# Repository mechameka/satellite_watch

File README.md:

# satellite_watch
ESP32-S3 based smartwatch with swappable, modular faceplate

Phase 1: Create prototype large-format board for diagnosing
Phase 2: Create compact mainboard
Phase 3: Create intial faceplate designs of LED, IPS, and blank protoboard/headers

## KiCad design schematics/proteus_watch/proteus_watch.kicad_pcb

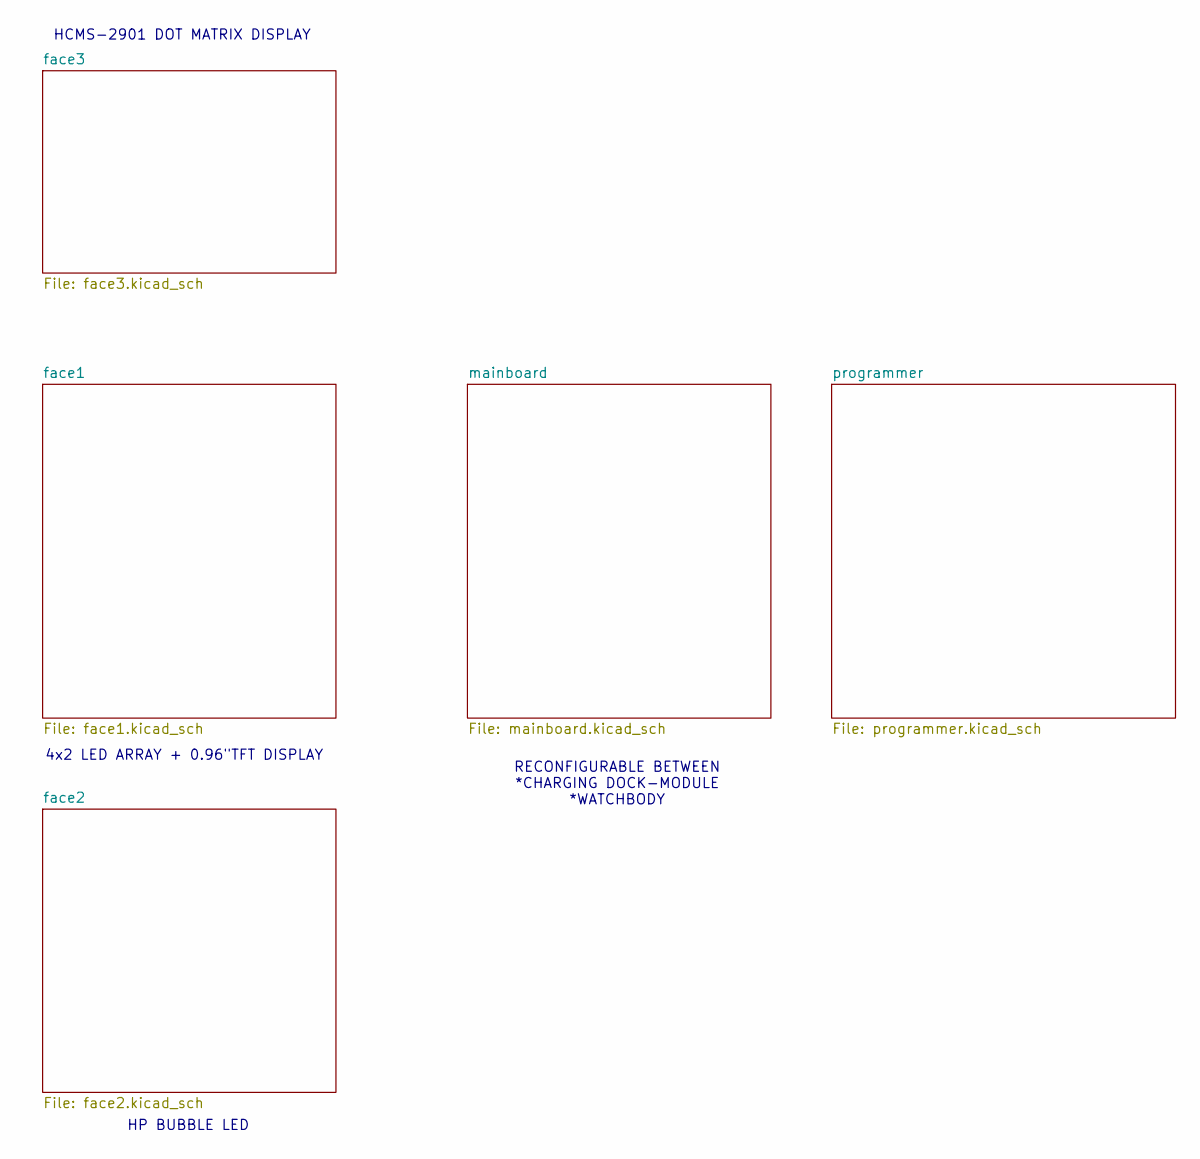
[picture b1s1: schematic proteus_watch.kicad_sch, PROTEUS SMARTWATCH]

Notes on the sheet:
RECONFIGURABLE BETWEEN *CHARGING DOCK-MODULE *WATCHBODY
4x2 LED ARRAY + 0.96"TFT DISPLAY
HCMS-2901 DOT MATRIX DISPLAY
HP BUBBLE LED

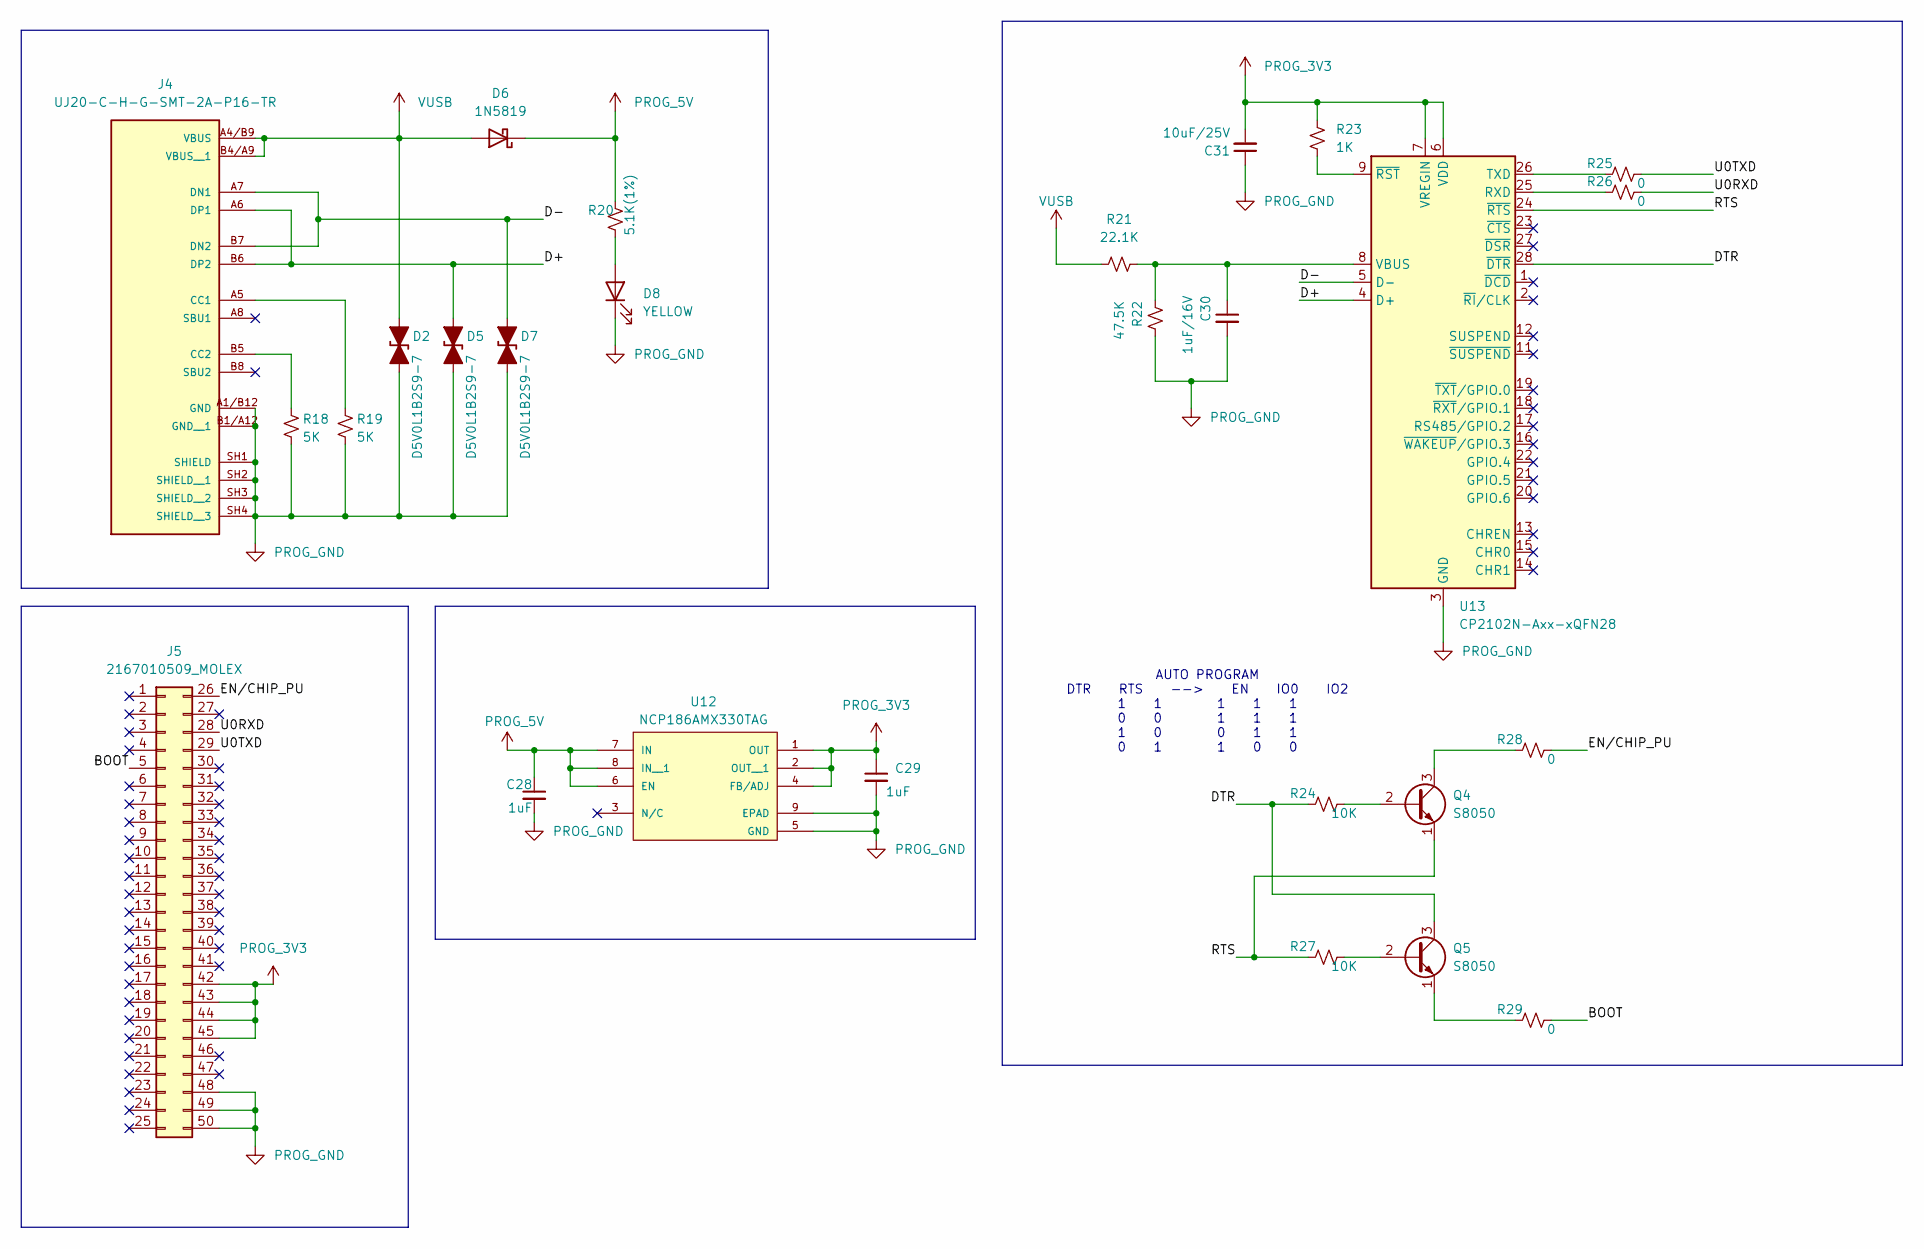
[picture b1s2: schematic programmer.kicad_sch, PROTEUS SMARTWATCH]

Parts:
C28, C29: 1uF; C_0402_1005Metric_Pad0.74x0.62mm_HandSolder
C30: 1uF/16V; C_0402_1005Metric_Pad0.74x0.62mm_HandSolder
C31: 10uF/25V; C_0402_1005Metric_Pad0.74x0.62mm_HandSolder
D2, D5, D7: D5V0L1B2S9-7; D_SOD-923
D6: 1N5819; D_SOD-123
D8: YELLOW; LED_0402_1005Metric_Pad0.77x0.64mm_HandSolder
J4: UJ20-C-H-G-SMT-2A-P16-TR; SAMESKY_UJ20-C-H-G-SMT-2A-P16-TR_1; PARTREV 1.0
J5: 2167010509_MOLEX; CON_2167010509_MOL
Q4, Q5: S8050; SOT-23
R18, R19: 5K; R_0402_1005Metric_Pad0.72x0.64mm_HandSolder
R20: 5.1K(1%); R_0402_1005Metric_Pad0.72x0.64mm_HandSolder
R21: 22.1K; R_0402_1005Metric_Pad0.72x0.64mm_HandSolder
R22: 47.5K; R_0402_1005Metric_Pad0.72x0.64mm_HandSolder
R23: 1K; R_0402_1005Metric_Pad0.72x0.64mm_HandSolder
R24, R27: 10K; R_0402_1005Metric_Pad0.72x0.64mm_HandSolder
R25, R26, R28, R29: 0; R_0402_1005Metric_Pad0.72x0.64mm_HandSolder
U12: NCP186AMX330TAG; PSON40P160X120X45-9N; PARTREV Rev.5
U13: CP2102N-Axx-xQFN28; QFN-28-1EP_5x5mm_P0.5mm_EP3.25x3.25mm_ThermalVias

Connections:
/programmer/BOOT: J5.5, R29.1
/programmer/D+: D5.1 (A1), J4.A6 (DP1), J4.B6 (DP2), U13.4 (D+)
/programmer/D-: D7.1 (A1), J4.A7 (DN1), J4.B7 (DN2), U13.5 (D-)
/programmer/DTR: Q5.3 (C), R24.2, U13.28 (~DTR)
/programmer/EN/CHIP_PU: J5.26, R28.1
/programmer/RTS: Q4.1 (E), R27.2, U13.24 (~RTS)
/programmer/U0RXD: J5.28, R26.1
/programmer/U0TXD: J5.29, R25.1
unnamed: D8.2 (A), R20.1
unnamed: J4.A5 (CC1), R19.1
unnamed: J4.B5 (CC2), R18.1
unnamed: Q4.2 (B), R24.1
unnamed: Q4.3 (C), R28.2
unnamed: Q5.2 (B), R27.1
unnamed: Q5.1 (E), R29.2
unnamed: R26.2, U13.25 (RXD)
unnamed: R25.2, U13.26 (TXD)
unnamed: C30.1, R21.2, R22.1, U13.8 (VBUS)
unnamed: R23.1, U13.9 (~RST)
PROG_3V3: C29.1, C31.2, J5.42, J5.43, J5.44, J5.45, R23.2, U12.1 (OUT), U12.2 (OUT__1), U12.4 (FB/ADJ), U13.6 (VDD), U13.7 (VREGIN)
PROG_5V: C28.1, D6.1 (K), R20.2, U12.6 (EN), U12.7 (IN), U12.8 (IN__1)
PROG_GND: C28.2, C29.2, C30.2, C31.1, D2.2 (A2), D5.2 (A2), D7.2 (A2), D8.1 (K), J4.A1/B12 (GND), J4.B1/A12 (GND__1), J4.SH1 (SHIELD), J4.SH2 (SHIELD__1), J4.SH3 (SHIELD__2), J4.SH4 (SHIELD__3), J5.48, J5.49, J5.50, R18.2, R19.2, R22.2, U12.5 (GND), U12.9 (EPAD), U13.3 (GND), U13.29 (GND)
VUSB: D2.1 (A1), D6.2 (A), J4.A4/B9 (VBUS), J4.B4/A9 (VBUS__1), R21.1

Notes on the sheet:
AUTO PROGRAM DTR RTS --> EN IO0 IO2 1 1 1 1 1 0 0 1 1 1 1 0 0 1 1 0 1 1 0 0

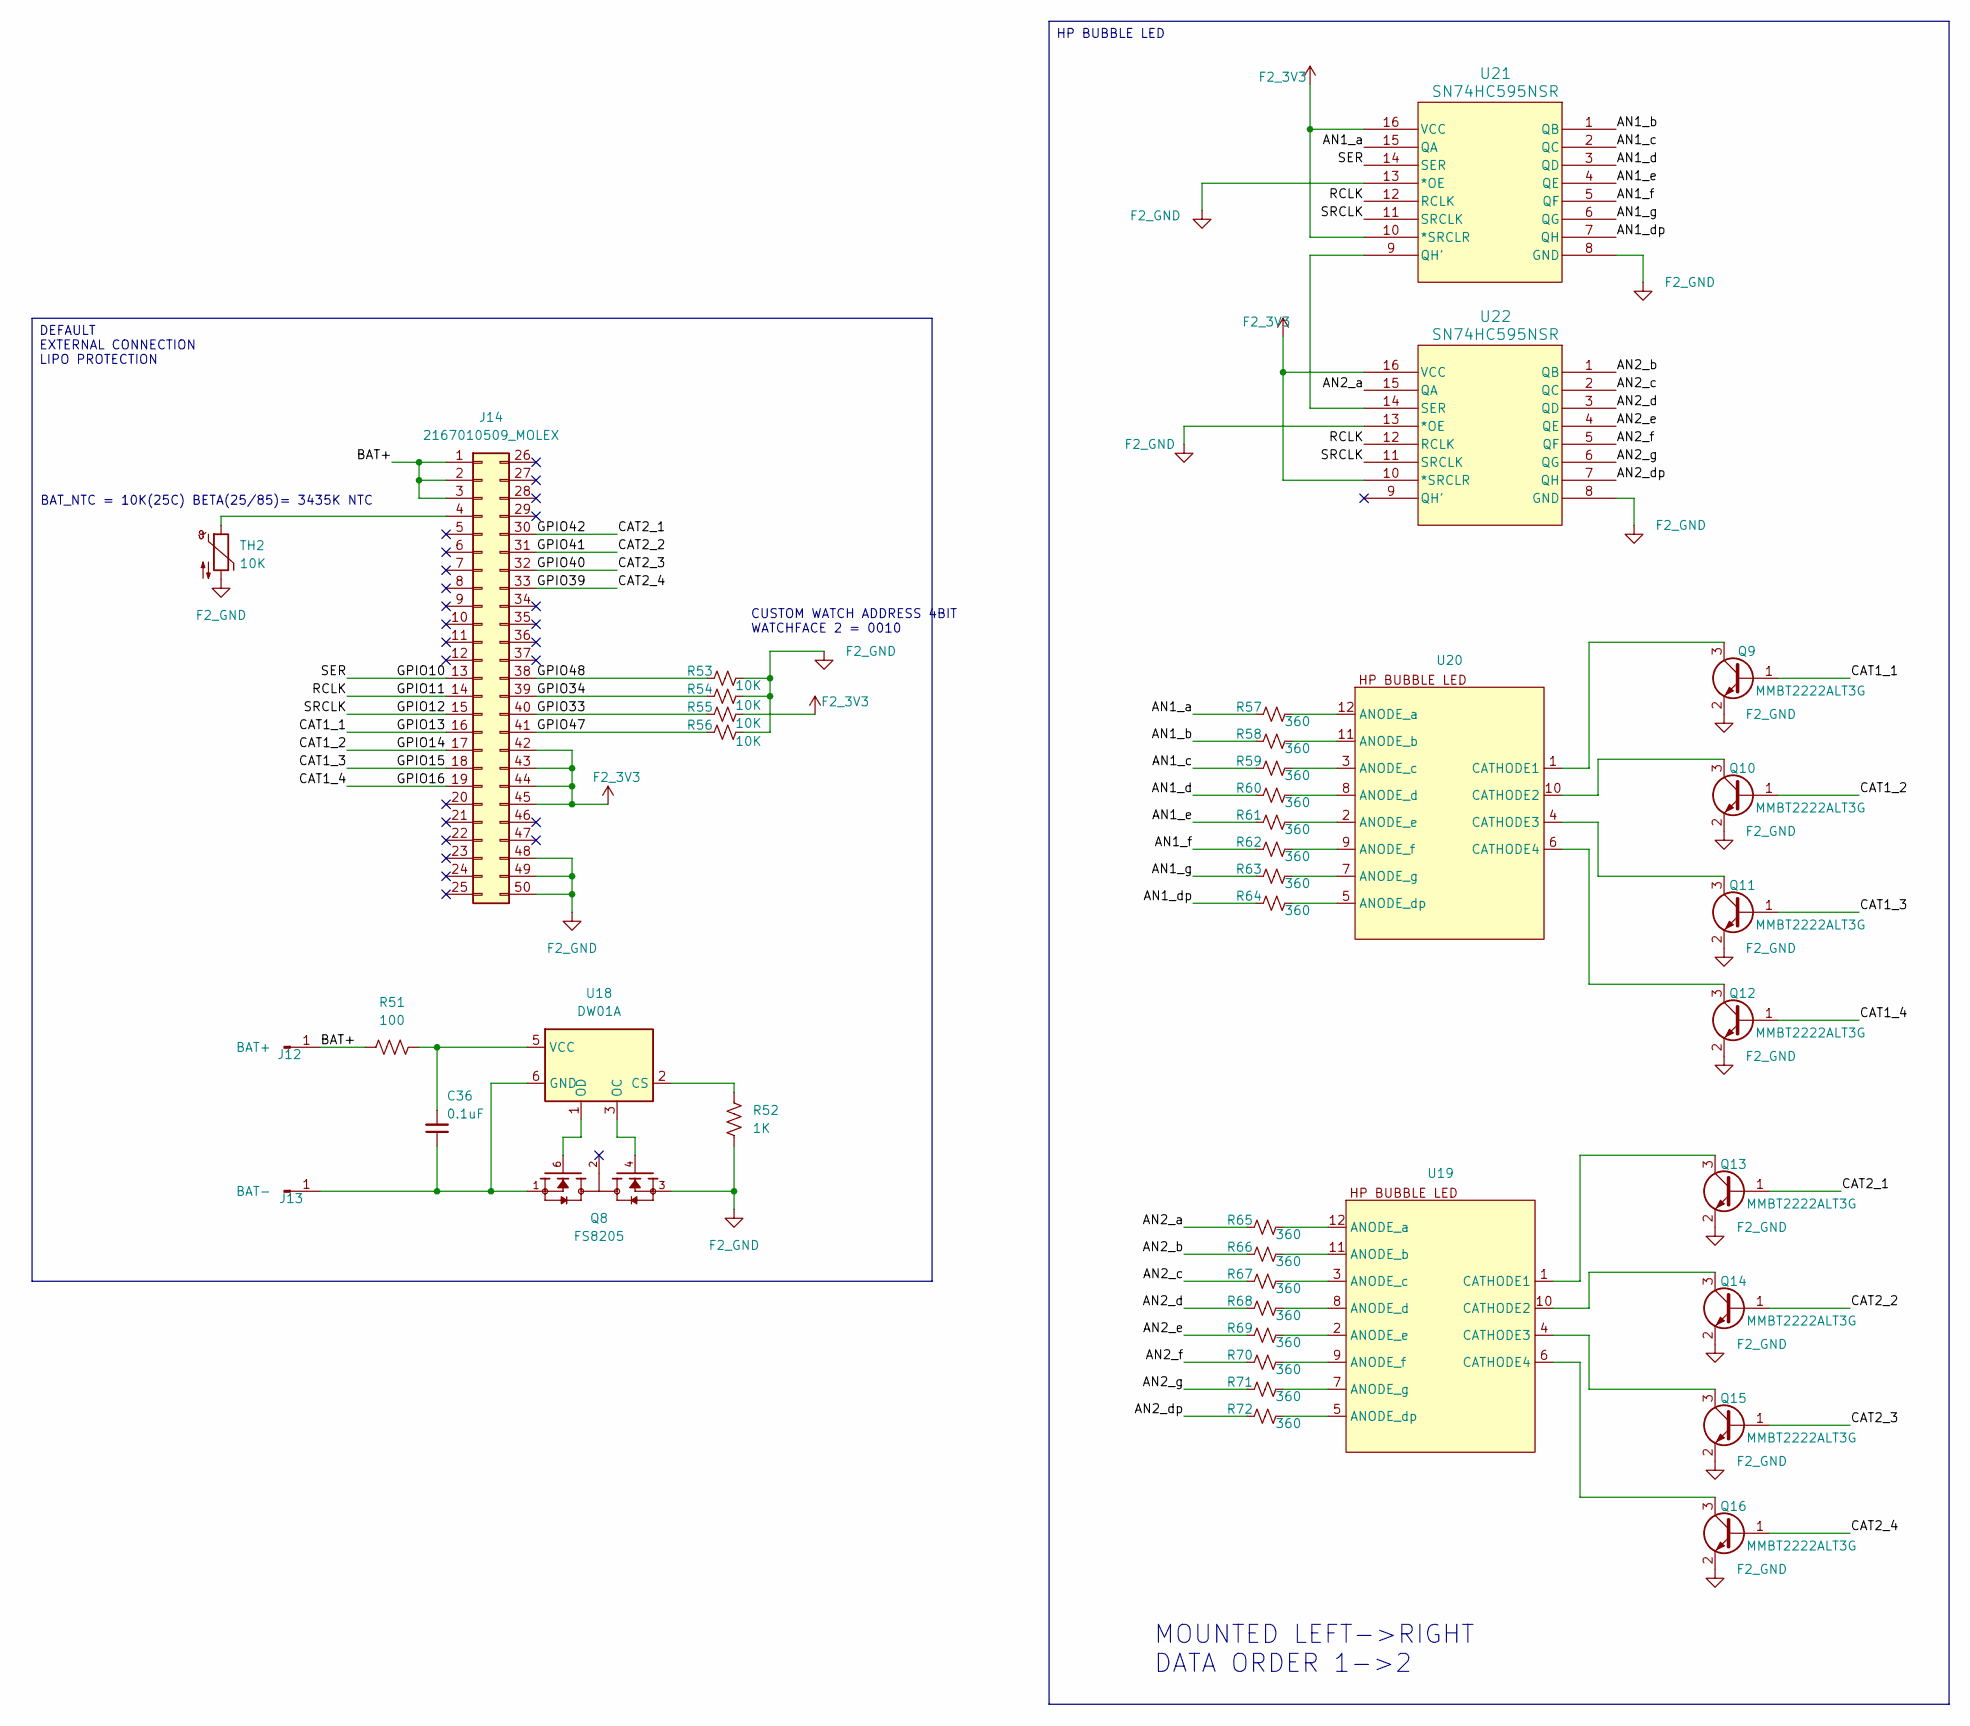
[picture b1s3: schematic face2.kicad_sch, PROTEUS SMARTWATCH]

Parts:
C36: 0.1uF; C_0402_1005Metric_Pad0.74x0.62mm_HandSolder
J12: BAT+; SolderWirePad_1x01_SMD_3x6mm
J13: BAT-; SolderWirePad_1x01_SMD_3x6mm
J14: 2167010509_MOLEX; CON_2167010509_MOL
Q8: FS8205; SOT95P280X145-6N; PARTREV 1.9
Q9, Q10, Q11, Q12, Q13, Q14, Q15, Q16: MMBT2222ALT3G; SOT-23
R51: 100; R_0402_1005Metric_Pad0.72x0.64mm_HandSolder
R52: 1K; R_0402_1005Metric_Pad0.72x0.64mm_HandSolder
R53, R54, R55, R56: 10K; R_0402_1005Metric_Pad0.72x0.64mm_HandSolder
R57, R58, R59, R60, R61, R62, R63, R64, R65, R66, R67, R68, R69, R70, R71, R72: 360; R_0402_1005Metric_Pad0.72x0.64mm_HandSolder
TH2: 10K; R_0402_1005Metric_Pad0.72x0.64mm_HandSolder
U18: DW01A; SOT-23-6
U19, U20: DIP-12_W7.62mm
U21, U22: SN74HC595NSR; NS16-L

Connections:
/face2/AN1_a: R57.1, U21.15 (QA)
/face2/AN1_b: R58.1, U21.1 (QB)
/face2/AN1_c: R59.1, U21.2 (QC)
/face2/AN1_d: R60.1, U21.3 (QD)
/face2/AN1_dp: R64.1, U21.7 (QH)
/face2/AN1_e: R61.1, U21.4 (QE)
/face2/AN1_f: R62.1, U21.5 (QF)
/face2/AN1_g: R63.1, U21.6 (QG)
/face2/AN2_a: R65.1, U22.15 (QA)
/face2/AN2_b: R66.1, U22.1 (QB)
/face2/AN2_c: R67.1, U22.2 (QC)
/face2/AN2_d: R68.1, U22.3 (QD)
/face2/AN2_dp: R72.1, U22.7 (QH)
/face2/AN2_e: R69.1, U22.4 (QE)
/face2/AN2_f: R70.1, U22.5 (QF)
/face2/AN2_g: R71.1, U22.6 (QG)
/face2/BAT+: J12.1 (Pin_1_1), J14.1, J14.2, J14.3, R51.1
/face2/CAT1_1: J14.16, Q9.1 (B)
/face2/CAT1_2: J14.17, Q10.1 (B)
/face2/CAT1_3: J14.18, Q11.1 (B)
/face2/CAT1_4: J14.19, Q12.1 (B)
/face2/CAT2_1: J14.30, Q13.1 (B)
/face2/CAT2_2: J14.31, Q14.1 (B)
/face2/CAT2_3: J14.32, Q15.1 (B)
/face2/CAT2_4: J14.33, Q16.1 (B)
/face2/GPIO10: J14.13, U21.14 (SER)
/face2/GPIO11: J14.14, U21.12 (RCLK), U22.12 (RCLK)
/face2/GPIO12: J14.15, U21.11 (SRCLK), U22.11 (SRCLK)
/face2/GPIO33: J14.40, R55.1
/face2/GPIO34: J14.39, R54.1
/face2/GPIO47: J14.41, R56.1
/face2/GPIO48: J14.38, R53.1
F2_3V3: J14.42, J14.43, J14.44, J14.45, R55.2, U21.10 (*SRCLR), U21.16 (VCC), U22.10 (*SRCLR), U22.16 (VCC)
F2_GND: J14.48, J14.49, J14.50, Q8.3, Q9.2 (E), Q10.2 (E), Q11.2 (E), Q12.2 (E), Q13.2 (E), Q14.2 (E), Q15.2 (E), Q16.2 (E), R52.1, R53.2, R54.2, R56.2, TH2.2, U21.8 (GND), U21.13 (*OE), U22.8 (GND), U22.13 (*OE)
unnamed: C36.1, J13.1 (Pin_1_1), Q8.1, U18.6 (GND)
unnamed: J14.4, TH2.1
unnamed: Q9.3 (C), U20.1 (CATHODE1)
unnamed: Q10.3 (C), U20.10 (CATHODE2)
unnamed: Q11.3 (C), U20.4 (CATHODE3)
unnamed: Q12.3 (C), U20.6 (CATHODE4)
unnamed: Q13.3 (C), U19.1 (CATHODE1)
unnamed: Q14.3 (C), U19.10 (CATHODE2)
unnamed: Q15.3 (C), U19.4 (CATHODE3)
unnamed: Q16.3 (C), U19.6 (CATHODE4)
unnamed: R52.2, U18.2 (CS)
unnamed: Q8.4, U18.3 (OC)
unnamed: Q8.6, U18.1 (OD)
unnamed: C36.2, R51.2, U18.5 (VCC)
unnamed: R65.2, U19.12 (ANODE_a)
unnamed: R66.2, U19.11 (ANODE_b)
unnamed: R67.2, U19.3 (ANODE_c)
unnamed: R68.2, U19.8 (ANODE_d)
unnamed: R72.2, U19.5 (ANODE_dp)
unnamed: R69.2, U19.2 (ANODE_e)
unnamed: R70.2, U19.9 (ANODE_f)
unnamed: R71.2, U19.7 (ANODE_g)
unnamed: R57.2, U20.12 (ANODE_a)
unnamed: R58.2, U20.11 (ANODE_b)
unnamed: R59.2, U20.3 (ANODE_c)
unnamed: R60.2, U20.8 (ANODE_d)
unnamed: R64.2, U20.5 (ANODE_dp)
unnamed: R61.2, U20.2 (ANODE_e)
unnamed: R62.2, U20.9 (ANODE_f)
unnamed: R63.2, U20.7 (ANODE_g)
unnamed: U21.9 (QH'), U22.14 (SER)

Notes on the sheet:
MOUNTED LEFT->RIGHT DATA ORDER 1->2
BAT_NTC = 10K(25C) BETA(25/85)= 3435K NTC
CUSTOM WATCH ADDRESS 4BIT WATCHFACE 2 = 0010
DEFAULT EXTERNAL CONNECTION LIPO PROTECTION
HP BUBBLE LED

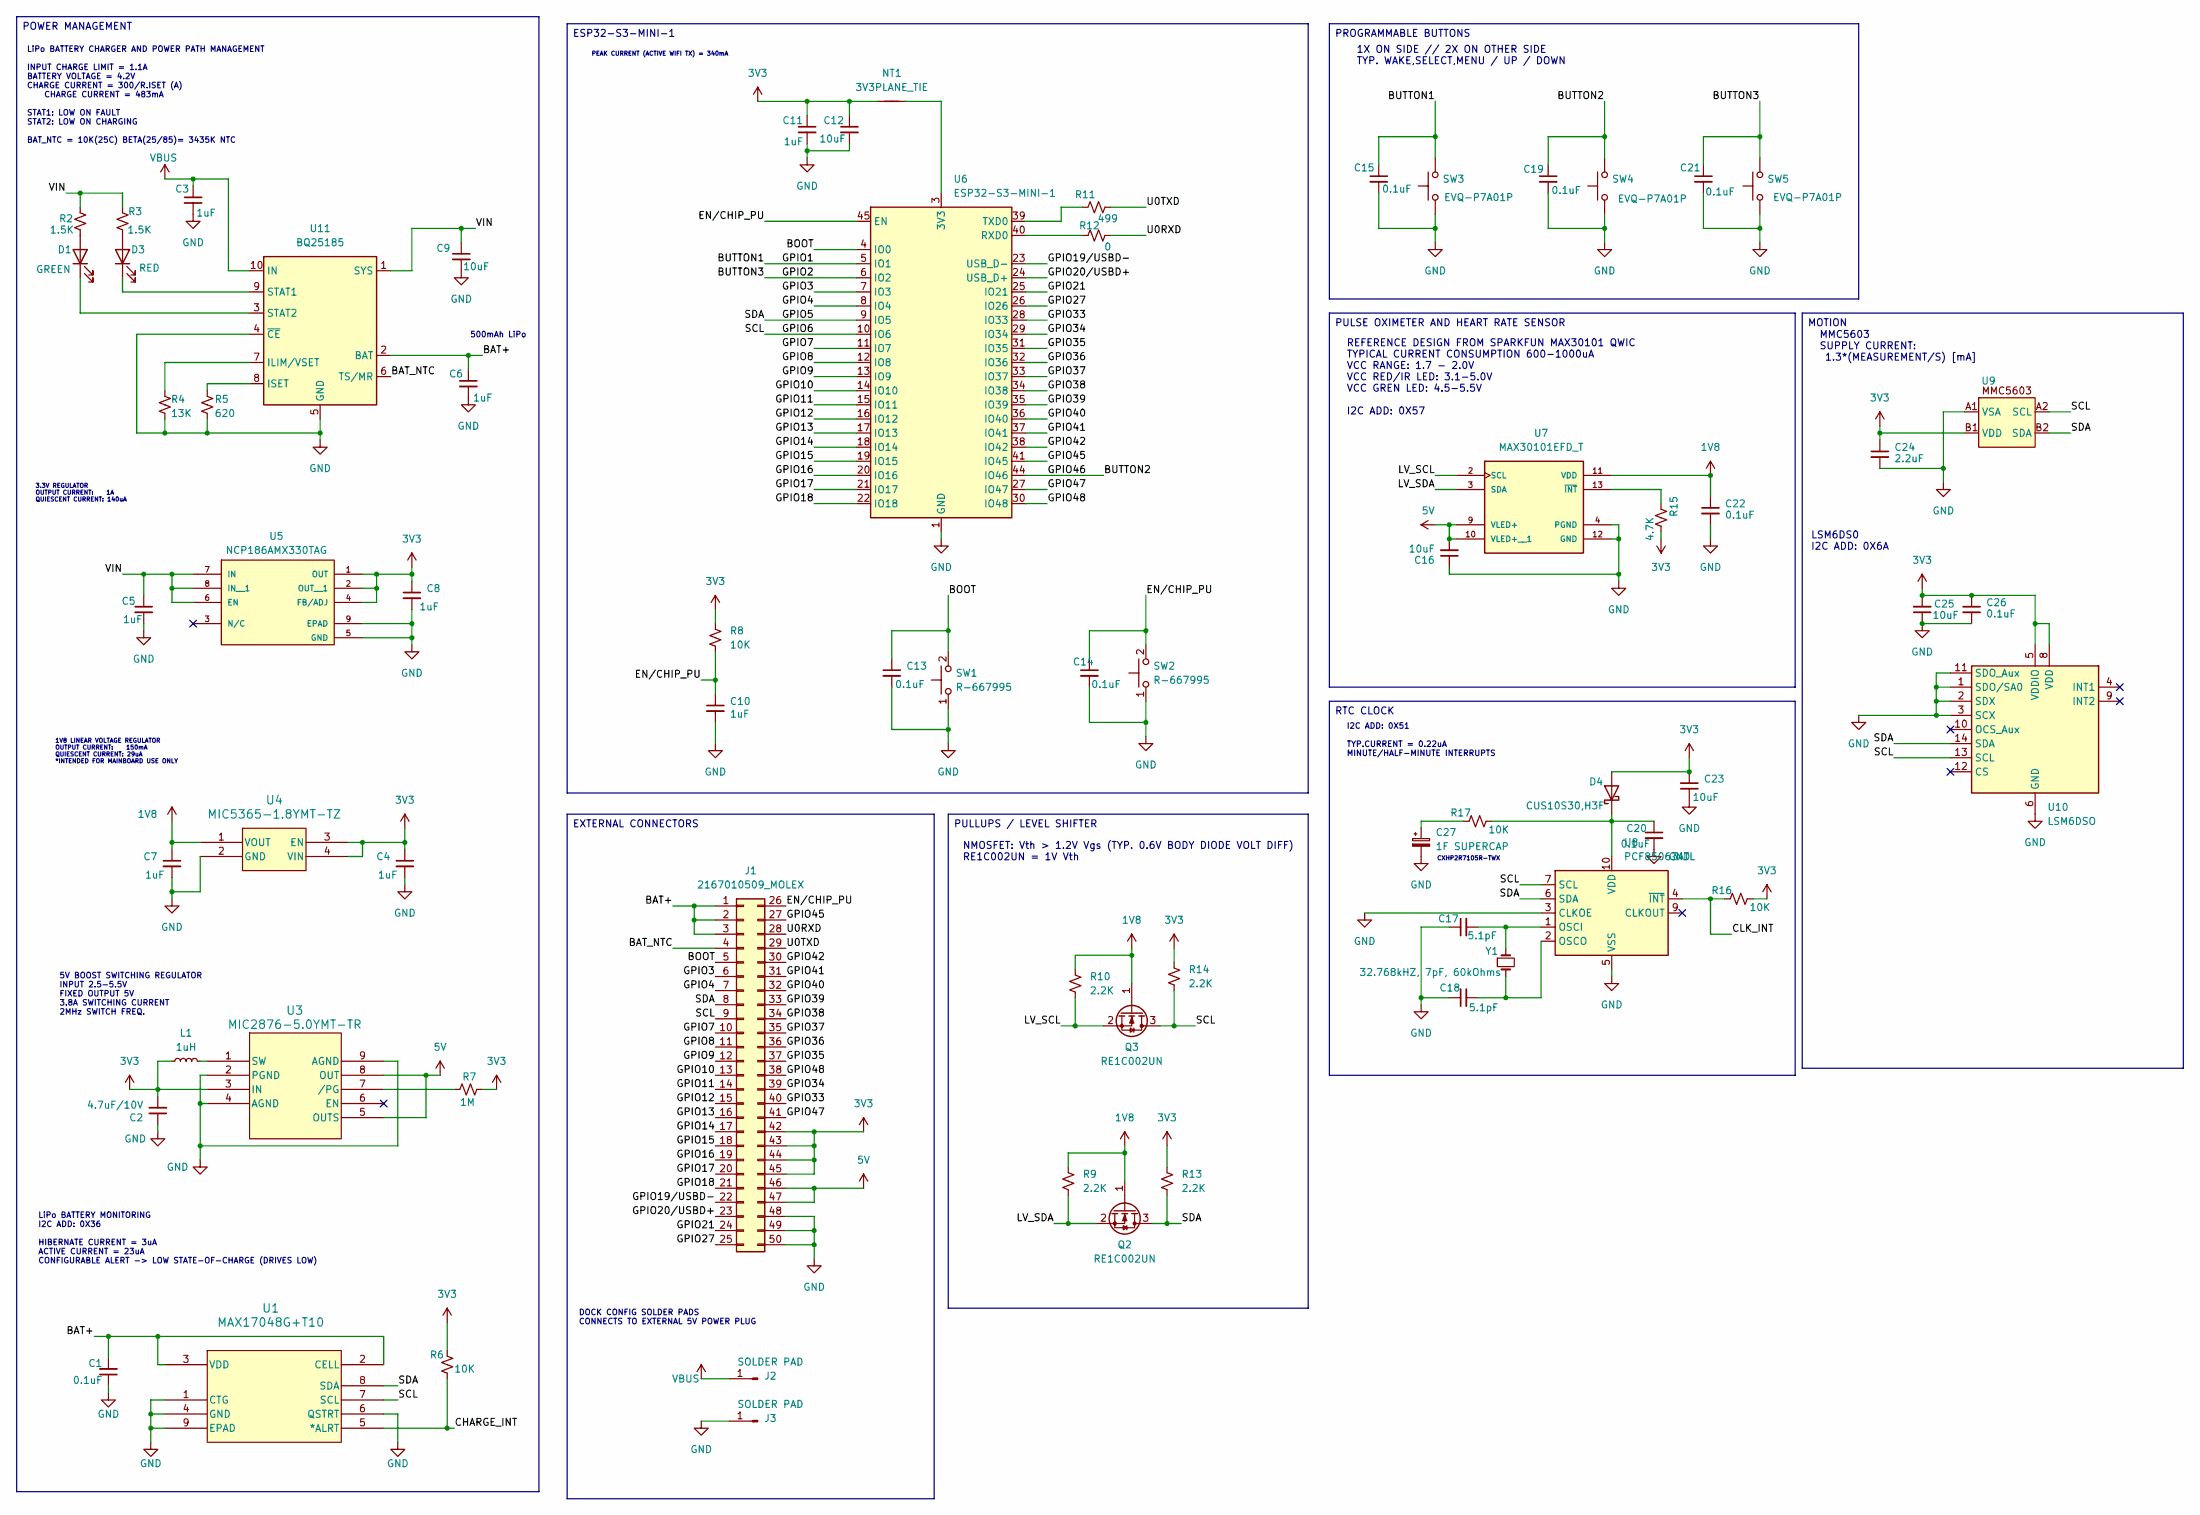
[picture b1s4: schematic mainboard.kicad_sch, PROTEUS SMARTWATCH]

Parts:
C1, C13, C14, C15, C19, C20, C21, C22, C26: 0.1uF; C_0402_1005Metric_Pad0.74x0.62mm_HandSolder
C2: 4.7uF/10V; C_0402_1005Metric_Pad0.74x0.62mm_HandSolder
C3, C4, C5, C6, C7, C8, C10, C11: 1uF; C_0402_1005Metric_Pad0.74x0.62mm_HandSolder
C9, C12, C16, C23, C25: 10uF; C_0402_1005Metric_Pad0.74x0.62mm_HandSolder
C17, C18: 5.1pF; C_0402_1005Metric_Pad0.74x0.62mm_HandSolder
C24: 2.2uF; C_0402_1005Metric_Pad0.74x0.62mm_HandSolder
C27: 1F SUPERCAP; 2.54mm_SUPERCAP_THT_RIGHTANGLE
D1: GREEN; LED_0402_1005Metric_Pad0.77x0.64mm_HandSolder
D3: RED; LED_0402_1005Metric_Pad0.77x0.64mm_HandSolder
D4: CUS10S30,H3F; D_SOD-323
J1: 2167010509_MOLEX; CON_2167010509_MOL
J2, J3: SOLDER PAD; SolderWirePad_1x01_SMD_1x2mm
L1: 1uH; L_0402_1005Metric_Pad0.77x0.64mm_HandSolder
NT1: 3V3PLANE_TIE; NetTie-2_SMD_Pad0.5mm
Q2, Q3: RE1C002UN; SOT-416
R2, R3: 1.5K; R_0402_1005Metric_Pad0.72x0.64mm_HandSolder
R4: 13K; R_0402_1005Metric_Pad0.72x0.64mm_HandSolder
R5: 620; R_0402_1005Metric_Pad0.72x0.64mm_HandSolder
R6, R8, R16, R17: 10K; R_0402_1005Metric_Pad0.72x0.64mm_HandSolder
R7: 1M; R_0402_1005Metric_Pad0.72x0.64mm_HandSolder
R9, R10, R13, R14: 2.2K; R_0402_1005Metric_Pad0.72x0.64mm_HandSolder
R11: 499; R_0402_1005Metric_Pad0.72x0.64mm_HandSolder
R12: 0; R_0402_1005Metric_Pad0.72x0.64mm_HandSolder
R15: 4.7K; R_0402_1005Metric_Pad0.72x0.64mm_HandSolder
SW1, SW2: R-667995; R-667995_MIT-L
SW3, SW4, SW5: EVQ-P7A01P; SW_SPST_EVQP7A
U1: MAX17048G+T10; TDFN-8-1EP_2x2mm_P0.5mm_EP0.8x1.2mm
U3: MIC2876-5.0YMT-TR; UDFN8_2X2_MCH-L
U4: MIC5365-1.8YMT-TZ; UDFN-4-1EP_1x1mm_P0.65mm_EP0.48x0.48mm
U5: NCP186AMX330TAG; PSON40P160X120X45-9N; PARTREV Rev.5
U6: ESP32-S3-MINI-1
U7: MAX30101EFD_T; MAX30101EFD+T; PARTREV 2
U8: PCF85063ATL; DFN-10-1EP_2.6x2.6mm_P0.5mm_EP1.3x2.2mm
U9: WLP-4_0.83x0.83mm_P0.4mm
U10: LSM6DSO; LGA-14_3x2.5mm_P0.5mm_LayoutBorder3x4y
U11: BQ25185; Texas_DLH0010A_WSON-10-1EP_2.2x2mm_P0.4mm_EP0.9x1.5mm_Therm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
Y1: 32.768kHZ, 7pF, 60kOhms; Crystal_SMD_GEYER_12.87147

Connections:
1V8: C7.1, C22.1, Q2.1 (G), Q3.1 (G), R9.1, R10.1, U4.1 (VOUT), U7.11 (VDD)
3V3: C2.2, C4.1, C8.1, C11.1, C12.1, C23.1, C24.1, C25.2, C26.1, D4.2 (A), J1.42, J1.43, J1.44, J1.45, L1.1, NT1.1, R6.2, R7.2, R8.1, R13.1, R14.1, R15.2, R16.2, U3.3 (IN), U4.3 (EN), U4.4 (VIN), U5.1 (OUT), U5.2 (OUT__1), U5.4 (FB/ADJ), U9.B1 (VDD), U10.5 (VDDIO), U10.8 (VDD)
5V: C16.2, J1.46, J1.47, U3.5 (OUTS), U3.8 (OUT), U7.9 (VLED+), U7.10 (VLED+__1)
/mainboard/BAT+: C1.2, C6.1, J1.1, J1.2, J1.3, U1.2 (CELL), U1.3 (VDD), U11.2 (BAT)
/mainboard/BAT_NTC: J1.4, U11.6 (TS/MR)
/mainboard/BOOT: C13.1, J1.5, SW1.2, U6.4 (IO0)
/mainboard/BUTTON1: C15.1, SW3.2, U6.5 (IO1)
/mainboard/BUTTON2: C19.1, SW4.2, U6.44 (IO46)
/mainboard/BUTTON3: C21.1, SW5.2, U6.6 (IO2)
/mainboard/CHARGE_INT: R6.1, U1.5 (*ALRT)
/mainboard/CLK_INT: R16.1, U8.4 (~INT)
/mainboard/EN/CHIP_PU: C10.1, C14.1, J1.26, R8.2, SW2.2, U6.45 (EN)
/mainboard/GPIO3: J1.6, U6.7 (IO3)
/mainboard/GPIO4: J1.7, U6.8 (IO4)
/mainboard/GPIO5: J1.8, Q2.3 (D), R13.2, U1.8 (SDA), U6.9 (IO5), U8.6 (SDA), U9.B2 (SDA), U10.14 (SDA)
/mainboard/GPIO6: J1.9, Q3.3 (D), R14.2, U1.7 (SCL), U6.10 (IO6), U8.7 (SCL), U9.A2 (SCL), U10.13 (SCL)
/mainboard/GPIO7: J1.10, U6.11 (IO7)
/mainboard/GPIO8: J1.11, U6.12 (IO8)
/mainboard/GPIO9: J1.12, U6.13 (IO9)
/mainboard/GPIO10: J1.13, U6.14 (IO10)
/mainboard/GPIO11: J1.14, U6.15 (IO11)
/mainboard/GPIO12: J1.15, U6.16 (IO12)
/mainboard/GPIO13: J1.16, U6.17 (IO13)
/mainboard/GPIO14: J1.17, U6.18 (IO14)
/mainboard/GPIO15: J1.18, U6.19 (IO15)
/mainboard/GPIO16: J1.19, U6.20 (IO16)
/mainboard/GPIO17: J1.20, U6.21 (IO17)
/mainboard/GPIO18: J1.21, U6.22 (IO18)
/mainboard/GPIO19/USBD-: J1.22, U6.23 (USB_D-)
/mainboard/GPIO20/USBD+: J1.23, U6.24 (USB_D+)
/mainboard/GPIO21: J1.24, U6.25 (IO21)
/mainboard/GPIO27: J1.25, U6.26 (IO26)
/mainboard/GPIO33: J1.40, U6.28 (IO33)
/mainboard/GPIO34: J1.39, U6.29 (IO34)
/mainboard/GPIO35: J1.37, U6.31 (IO35)
/mainboard/GPIO36: J1.36, U6.32 (IO36)
/mainboard/GPIO37: J1.35, U6.33 (IO37)
/mainboard/GPIO38: J1.34, U6.34 (IO38)
/mainboard/GPIO39: J1.33, U6.35 (IO39)
/mainboard/GPIO40: J1.32, U6.36 (IO40)
/mainboard/GPIO41: J1.31, U6.37 (IO41)
/mainboard/GPIO42: J1.30, U6.38 (IO42)
/mainboard/GPIO45: J1.27, U6.41 (IO45)
/mainboard/GPIO47: J1.41, U6.27 (IO47)
/mainboard/GPIO48: J1.38, U6.30 (IO48)
/mainboard/LV_SCL: Q3.2 (S), R10.2, U7.2 (SCL)
/mainboard/LV_SDA: Q2.2 (S), R9.2, U7.3 (SDA)
/mainboard/U0RXD: J1.28, R12.2
/mainboard/U0TXD: J1.29, R11.2
/mainboard/VIN: C5.1, C9.1, R2.2, R3.2, U5.6 (EN), U5.7 (IN), U5.8 (IN__1), U11.1 (SYS)
GND: C1.1, C2.1, C3.2, C4.2, C5.2, C6.2, C7.2, C8.2, C9.2, C10.2, C11.2, C12.2, C13.2, C14.2, C15.2, C16.1, C17.1, C18.1, C19.2, C20.2, C21.2, C22.2, C23.2, C24.2, C25.1, C26.2, C27.2, J1.48, J1.49, J1.50, J3.1 (Pin_1_1), R4.2, R5.2, SW1.1, SW2.1, SW3.1, SW4.1, SW5.1, U1.1 (CTG), U1.4 (GND), U1.6 (QSTRT), U1.9 (EPAD), U3.2 (PGND), U3.4 (AGND), U3.9 (AGND), U4.2 (GND), U4.5 (EP), U5.5 (GND), U5.9 (EPAD), U6.1 (GND), U6.2 (GND), U6.42 (GND), U6.43 (GND), U6.46 (GND), U6.47 (GND), U6.48 (GND), U6.49 (GND), U6.50 (GND), U6.51 (GND), U6.52 (GND), U6.53 (GND), U6.54 (GND), U6.55 (GND), U6.56 (GND), U6.57 (GND), U6.58 (GND), U6.59 (GND), U6.60 (GND), U6.61 (GND), U6.62 (GND), U6.63 (GND), U6.64 (GND), U6.65 (GND), U7.4 (PGND), U7.12 (GND), U8.3 (CLKOE), U8.5 (VSS), U8.11 (EP), U9.A1 (VSA), U10.1 (SDO/SA0), U10.2 (SDX), U10.3 (SCX), U10.6 (GND), U10.7 (GND), U10.11 (SDO_Aux), U11.4 (~CE), U11.5 (GND), U11.11 (EP)
unnamed: C27.1, R17.1
unnamed: D1.2 (A), R2.1
unnamed: D1.1 (K), U11.3 (STAT2)
unnamed: D3.2 (A), R3.1
unnamed: D3.1 (K), U11.9 (STAT1)
unnamed: C20.1, D4.1 (K), R17.2, U8.10 (VDD)
unnamed: L1.2, U3.1 (SW)
unnamed: R7.1, U3.7 (/PG)
unnamed: NT1.2, U6.3 (3V3)
unnamed: R12.1, U6.40 (RXD0)
unnamed: R11.1, U6.39 (TXD0)
unnamed: R15.1, U7.13 (~INT)
unnamed: C17.2, U8.1 (OSCI), Y1.1
unnamed: C18.2, U8.2 (OSCO), Y1.2
unnamed: R4.1, U11.7 (ILIM/VSET)
unnamed: R5.1, U11.8 (ISET)
VBUS: C3.1, J2.1 (Pin_1_1), U11.10 (IN)

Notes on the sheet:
PEAK CURRENT (ACTIVE WIFI TX) = 340mA
REFERENCE DESIGN FROM SPARKFUN MAX30101 QWIC TYPICAL CURRENT CONSUMPTION 600-1000uA VCC RANGE: 1.7 - 2.0V VCC RED/IR LED: 3.1-5.0V VCC GREN LED: 4.5-5.5V I2C ADD: 0X57
500mAh LiPo
LSM6DS0 I2C ADD: 0X6A
LiPo BATTERY CHARGER AND POWER PATH MANAGEMENT INPUT CHARGE LIMIT = 1.1A BATTERY VOLTAGE = 4.2V CHARGE CURRENT = 300/R.ISET (A) CHARGE CURRENT = 483mA STAT1: LOW ON FAULT STAT2: LOW ON CHARGING BAT_NTC = 10K(25C) BETA(25/85)= 3435K NTC
1X ON SIDE // 2X ON OTHER SIDE TYP. WAKE,SELECT,MENU / UP / DOWN
LiPo BATTERY MONITORING I2C ADD: 0X36 HIBERNATE CURRENT = 3uA ACTIVE CURRENT = 23uA CONFIGURABLE ALERT -> LOW STATE-OF-CHARGE (DRIVES LOW)
CXHP2R7105R-TWX
DOCK CONFIG SOLDER PADS CONNECTS TO EXTERNAL 5V POWER PLUG
MMC5603 SUPPLY CURRENT: 1.3*(MEASUREMENT/S) [mA]
NMOSFET: Vth > 1.2V Vgs (TYP. 0.6V BODY DIODE VOLT DIFF) RE1C002UN = 1V Vth
1V8 LINEAR VOLTAGE REGULATOR OUTPUT CURRENT: 150mA QUIESCENT CURRENT: 29uA *INTENDED FOR MAINBOARD USE ONLY
5V BOOST SWITCHING REGULATOR INPUT 2.5-5.5V FIXED OUTPUT 5V 3.8A SWITCHING CURRENT 2MHz SWITCH FREQ.
3.3V REGULATOR OUTPUT CURRENT: 1A QUIESCENT CURRENT: 140uA
I2C ADD: 0X51 TYP.CURRENT = 0.22uA MINUTE/HALF-MINUTE INTERRUPTS
MOTION
POWER MANAGEMENT
RTC CLOCK
PROGRAMMABLE BUTTONS
ESP32-S3-MINI-1
PULSE OXIMETER AND HEART RATE SENSOR
PULLUPS / LEVEL SHIFTER
EXTERNAL CONNECTORS

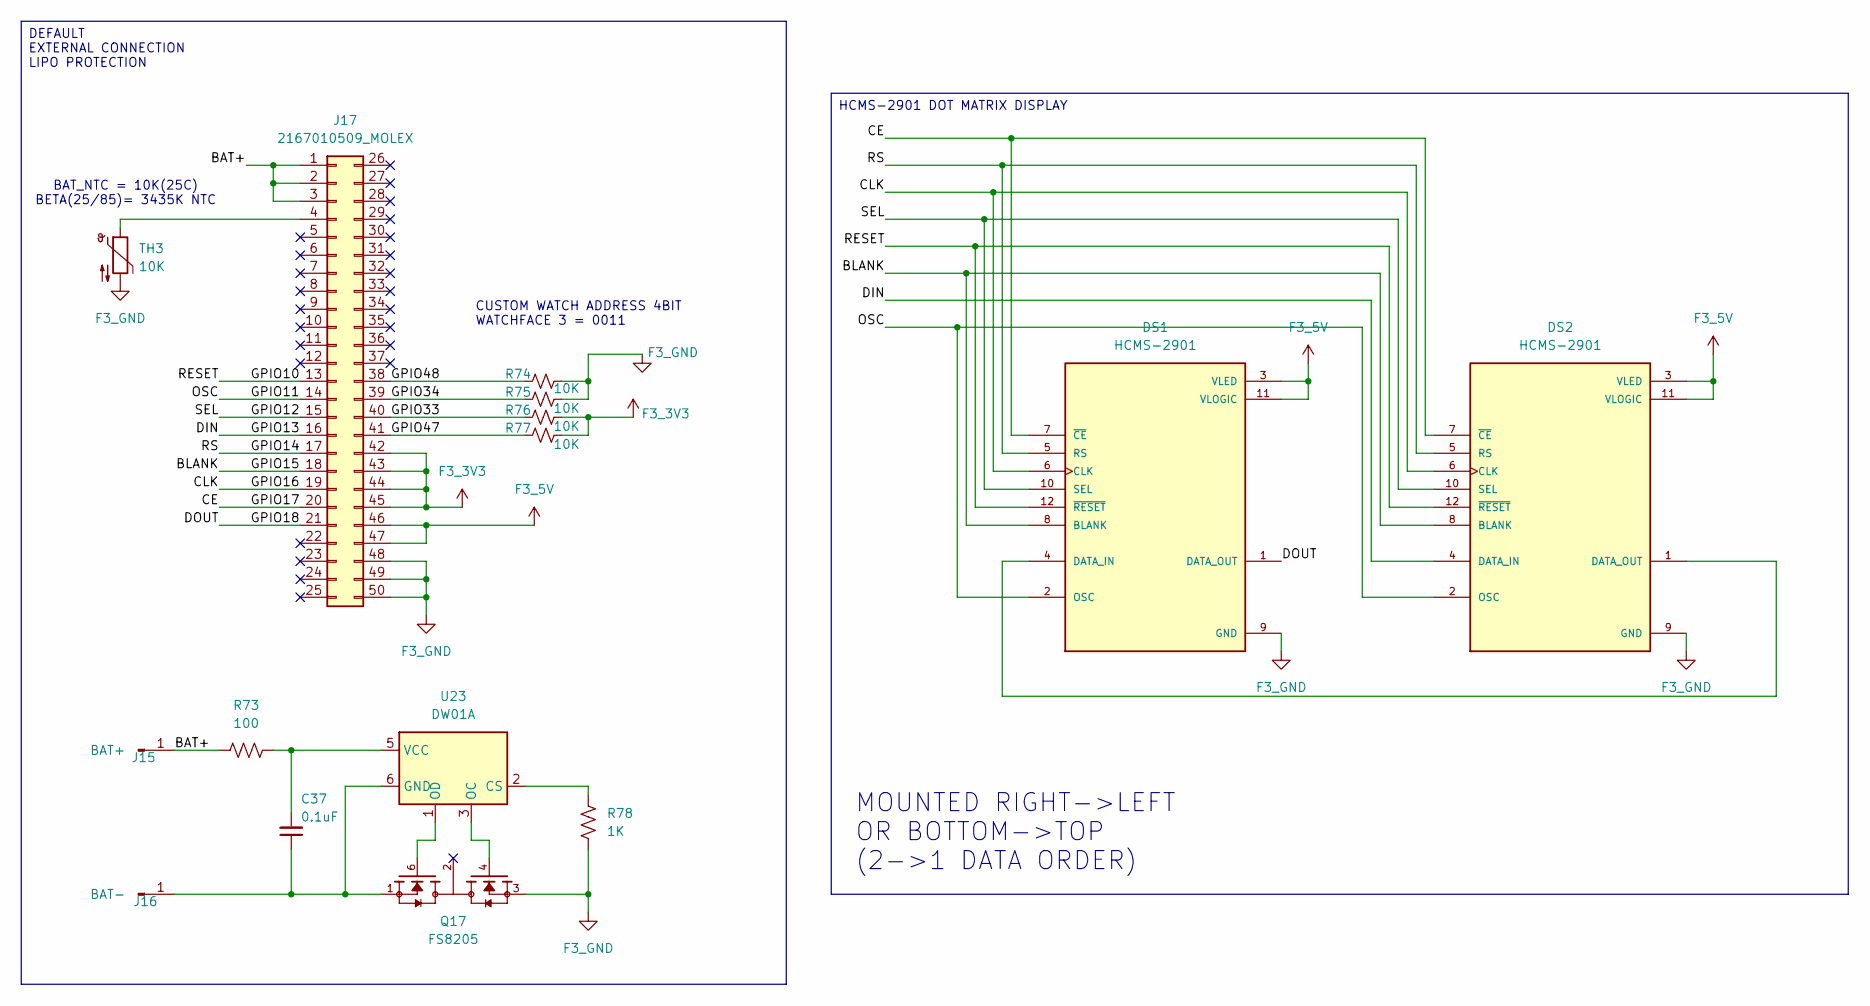
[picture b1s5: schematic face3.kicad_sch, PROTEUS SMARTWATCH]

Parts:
C37: 0.1uF; C_0402_1005Metric_Pad0.74x0.62mm_HandSolder
DS1, DS2: HCMS-2901; DIP-12_W7.62mm; PARTREV N/A
J15: BAT+; SolderWirePad_1x01_SMD_3x6mm
J16: BAT-; SolderWirePad_1x01_SMD_3x6mm
J17: 2167010509_MOLEX; CON_2167010509_MOL
Q17: FS8205; SOT95P280X145-6N; PARTREV 1.9
R73: 100; R_0402_1005Metric_Pad0.72x0.64mm_HandSolder
R74, R75, R76, R77: 10K; R_0402_1005Metric_Pad0.72x0.64mm_HandSolder
R78: 1K; R_0402_1005Metric_Pad0.72x0.64mm_HandSolder
TH3: 10K; R_0402_1005Metric_Pad0.72x0.64mm_HandSolder
U23: DW01A; SOT-23-6

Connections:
/face3/BAT+: J15.1 (Pin_1_1), J17.1, J17.2, J17.3, R73.1
/face3/BLANK: DS1.8 (BLANK), DS2.8 (BLANK), J17.18
/face3/CE: DS1.7 (~CE), DS2.7 (~CE), J17.20
/face3/CLK: DS1.6 (CLK), DS2.6 (CLK), J17.19
/face3/DIN: DS2.4 (DATA_IN), J17.16
/face3/DOUT: DS1.1 (DATA_OUT), J17.21
/face3/GPIO10: DS1.12 (~RESET), DS2.12 (~RESET), J17.13
/face3/GPIO11: DS1.2 (OSC), DS2.2 (OSC), J17.14
/face3/GPIO12: DS1.10 (SEL), DS2.10 (SEL), J17.15
/face3/GPIO14: DS1.5 (RS), DS2.5 (RS), J17.17
/face3/GPIO33: J17.40, R76.1
/face3/GPIO34: J17.39, R75.1
/face3/GPIO47: J17.41, R77.1
/face3/GPIO48: J17.38, R74.1
F3_3V3: J17.42, J17.43, J17.44, J17.45, R76.2, R77.2
F3_5V: DS1.3 (VLED), DS1.11 (VLOGIC), DS2.3 (VLED), DS2.11 (VLOGIC), J17.46, J17.47
F3_GND: DS1.9 (GND), DS2.9 (GND), J17.48, J17.49, J17.50, Q17.3, R74.2, R75.2, R78.1, TH3.2
unnamed: DS1.4 (DATA_IN), DS2.1 (DATA_OUT)
unnamed: C37.1, J16.1 (Pin_1_1), Q17.1, U23.6 (GND)
unnamed: J17.4, TH3.1
unnamed: R78.2, U23.2 (CS)
unnamed: Q17.4, U23.3 (OC)
unnamed: Q17.6, U23.1 (OD)
unnamed: C37.2, R73.2, U23.5 (VCC)

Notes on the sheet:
BAT_NTC = 10K(25C) BETA(25/85)= 3435K NTC
MOUNTED RIGHT->LEFT OR BOTTOM->TOP (2->1 DATA ORDER)
CUSTOM WATCH ADDRESS 4BIT WATCHFACE 3 = 0011
HCMS-2901 DOT MATRIX DISPLAY
DEFAULT EXTERNAL CONNECTION LIPO PROTECTION
